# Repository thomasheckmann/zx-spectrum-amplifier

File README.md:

# zx-spectrum-amplifier
DIY Amplifier from danish magazine for ZX Spectrum re-created in KiCad as close as possible to original design. This constructions was published in Ny Elektronik issue 3 in 1984.

# Original construction
This is the constructions as published in the magazine in 1984.
<table>
  <tr>
    <td colspan="3" align="center"></td>
  </tr>
  <tr>
    <td align="center"></td>
    <td align="center"></td>
    <td align="center"> </td>
  </tr>
  <tr>
    <td align="center">Schema</td>
    <td align="center">PCB</td>
    <td align="center">Components layout</td>
  </tr>
</table>

# Recreated construction

## First prototype
The main goal was to get the schema redrawn in KiCad and a first try at a PCB, in order to build a version to check if everything works.

| Schema | KiCad | PCB |
| ------ | ----- | --- |
|||</img>

First version of PBC was done by manually layout of tracks, according to the original component layouts from the magazine

## Second prototype
As the first version worked perfektly, the main goal was to add relevant plugs for EAR and DC power and resize the board to fit in a suitable enclosure. I even had to create a new footprint for the DC plug, but than again - great learning. Also a small trimmer-pot has been added, in order to be able to recude the noise that is generated in general - it can be skipped and replaced with a small wire, if you wish.

| KiCad  | PCB |
| ------ | --- |
||</img>

For the track layout, I decided to go with the autoroute plugin - as it makes a nice layout and makes a double sidded print as well.

The new PCB is adjusted to fit in a box of size 84mm X 56mm X 20mm. For example this enclosure box from [Hammond](https://www.hammfg.com/part/1591XXMGY)

## Final version (for now)
And this is how the final product turned out, fitting nicely in a standard enclosure.
| Enclosure | Assembled | In use |
| --------- | --------- | ------ |
|||

## BOM
You will need the following componets:
* R1 - 10 Ohm 1/4W
* P1 - 4,7 kOhm Potentiometer, logarithmic mono
* C1 - 4,7 nF - ceramic
* C2 - 22 uF/16V - electrolytic
* C3 - 22 uF/16V - electrolytic
* C4 100 uF/16V - electrolytic
* C5 0,1 uF/35V tantalum
* IC1 - LM386N
* Trimmer Top Adjust P5/10 50K (Optional)
* Speaker 8 Ohm, pin headers, DC and Minijack plugs

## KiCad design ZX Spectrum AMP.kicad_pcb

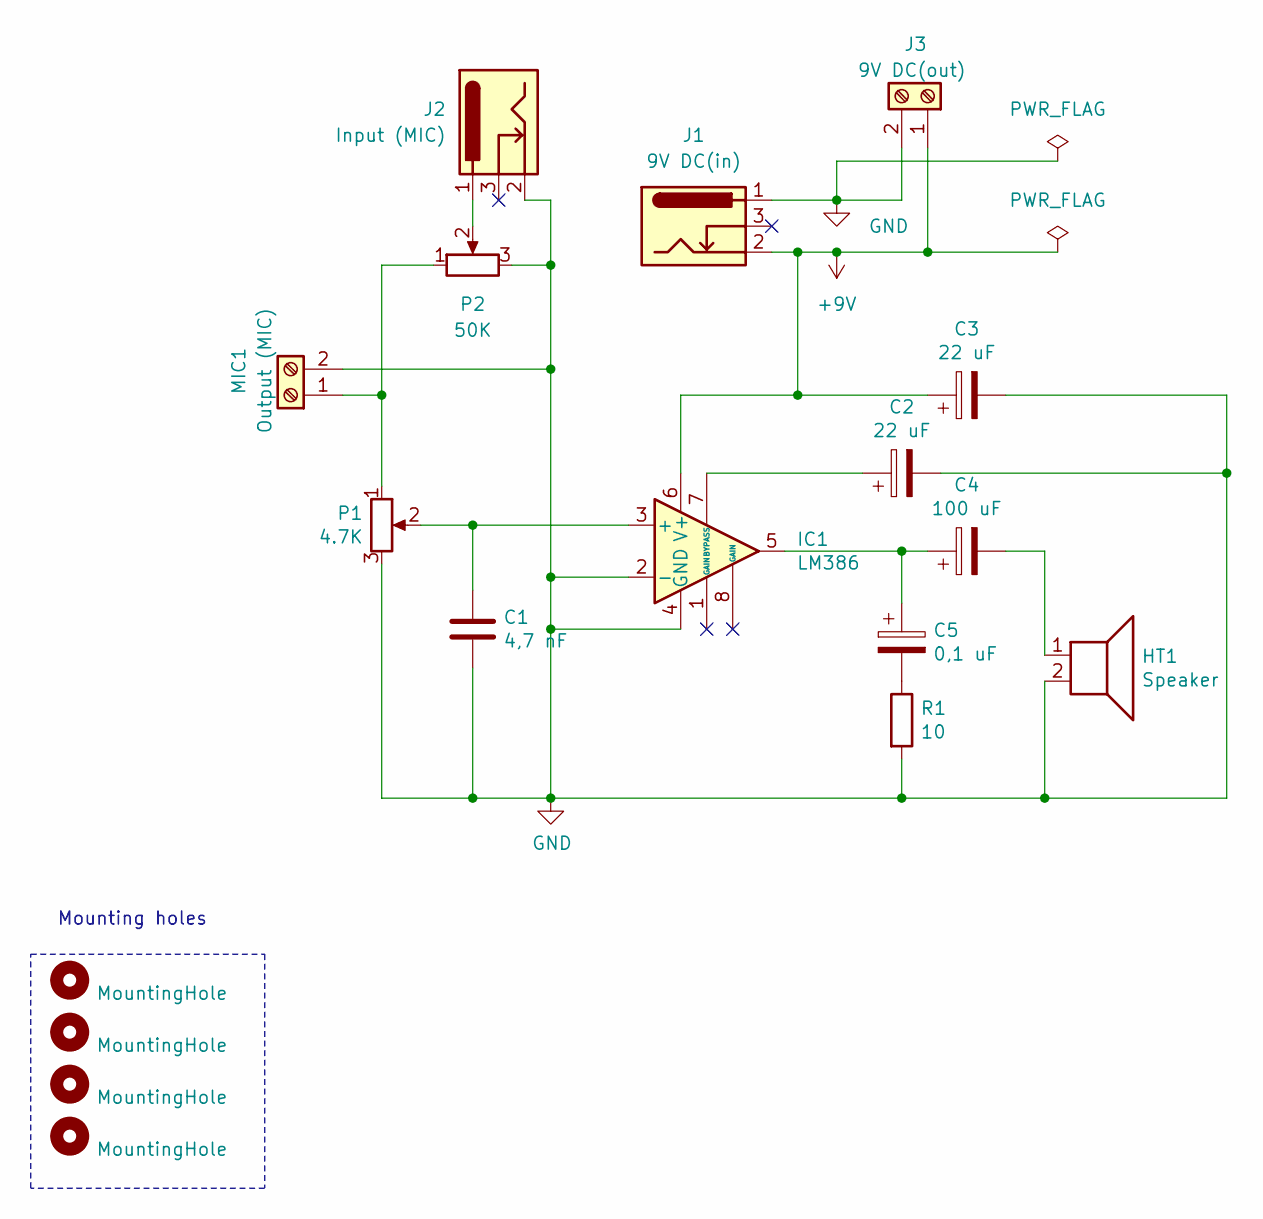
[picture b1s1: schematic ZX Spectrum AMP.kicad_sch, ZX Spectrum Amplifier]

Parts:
C1: 4,7 nF; C_Disc_D7.5mm_W5.0mm_P7.50mm
C2, C3: 22 uF; CP_Radial_D5.0mm_P2.50mm
C4: 100 uF; CP_Radial_D5.0mm_P2.50mm
C5: 0,1 uF; CP_Radial_Tantal_D4.5mm_P2.50mm
H1, H2, H3, H4: MountingHole; MountingHole_3.5mm
HT1: Speaker; PinHeader_1x02_P2.54mm_Horizontal
IC1: LM386; DIP-8_W7.62mm
J1: 9V DC(in); BarrelJack_GCT_DCJ200-10-A_Horizontal
J2: Input (MIC); 3.5mm mono jack chassis with switch
J3: 9V DC(out); PinHeader_1x02_P2.54mm_Horizontal
MIC1: Output (MIC); PinHeader_1x02_P2.54mm_Horizontal
P1: 4.7K; Potentionmeter
P2: 50K; Potentiometer_Piher_PT-10-V10_Vertical
R1: 10; R_Axial_DIN0207_L6.3mm_D2.5mm_P10.16mm_Horizontal

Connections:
+9V: C3.1, IC1.6 (V+), J1.2, J3.1
GND: C1.2, C2.2, C3.2, HT1.2, IC1.2 (-), IC1.4 (GND), J1.1, J2.2, J3.2, MIC1.2, P1.3, P2.3, R1.2
unnamed: C4.1, C5.1, IC1.5
unnamed: C4.2, HT1.1
unnamed: C5.2, R1.1
unnamed: C1.1, IC1.3 (+), P1.2
unnamed: C2.1, IC1.7 (BYPASS)
unnamed: J2.1, P2.2
unnamed: MIC1.1, P1.1, P2.1

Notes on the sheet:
Mounting holes

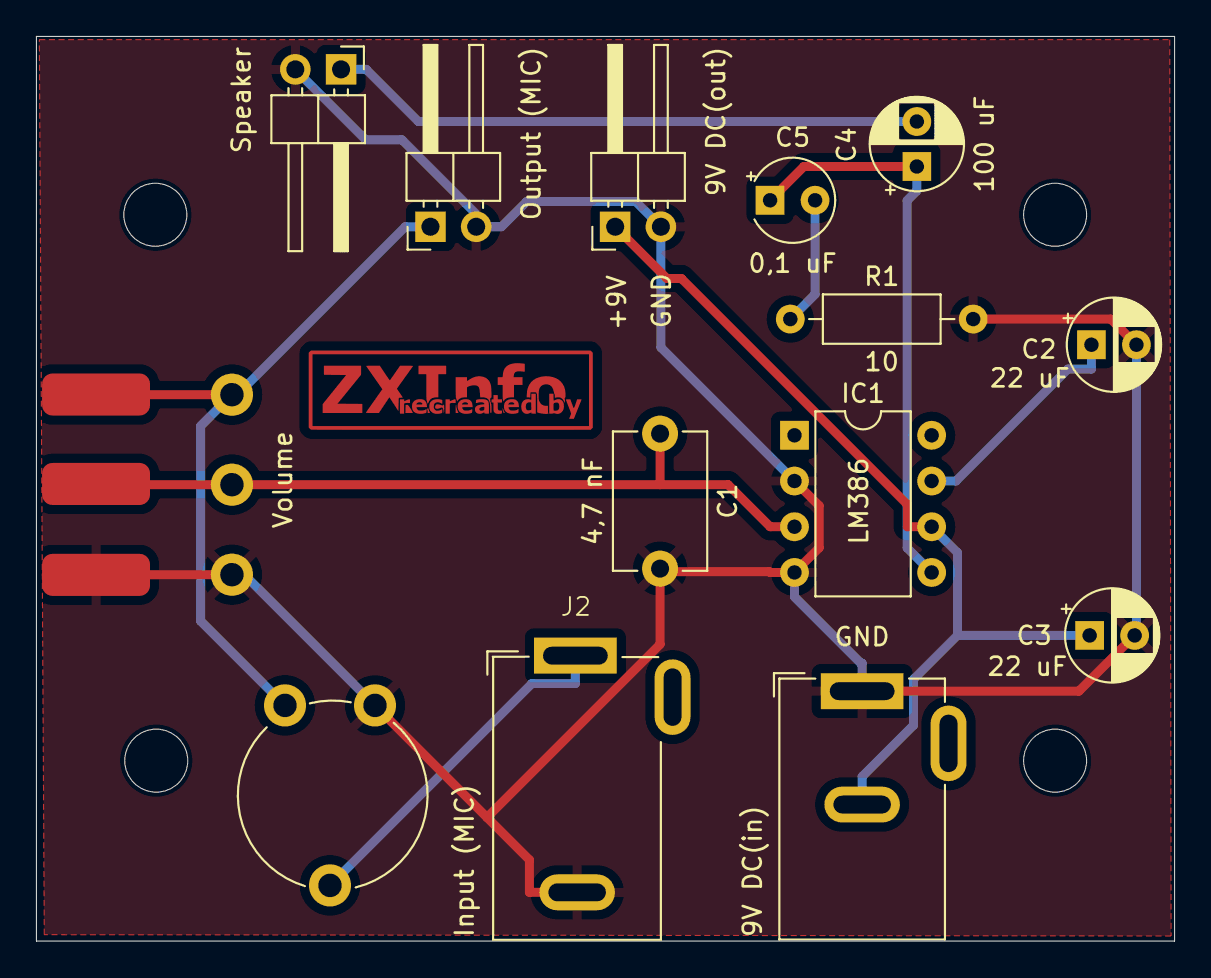
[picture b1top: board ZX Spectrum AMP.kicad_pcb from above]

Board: 2 copper layers, 63.2 x 50.3 mm, 19 parts (0 on the bottom side), 9 nets.

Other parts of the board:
G200: LOGO; ZXInfo_kicad_logo_copper_16.5x5

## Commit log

2024-02-29 Gerber for V2 sendt to production
2024-03-04 Updated _autosave pattern
2024-03-04 Update README.md
    added images from original magazine
2024-04-02 v0.3 - add logo + corrected text
2024-04-04 Final v3 - gerber
